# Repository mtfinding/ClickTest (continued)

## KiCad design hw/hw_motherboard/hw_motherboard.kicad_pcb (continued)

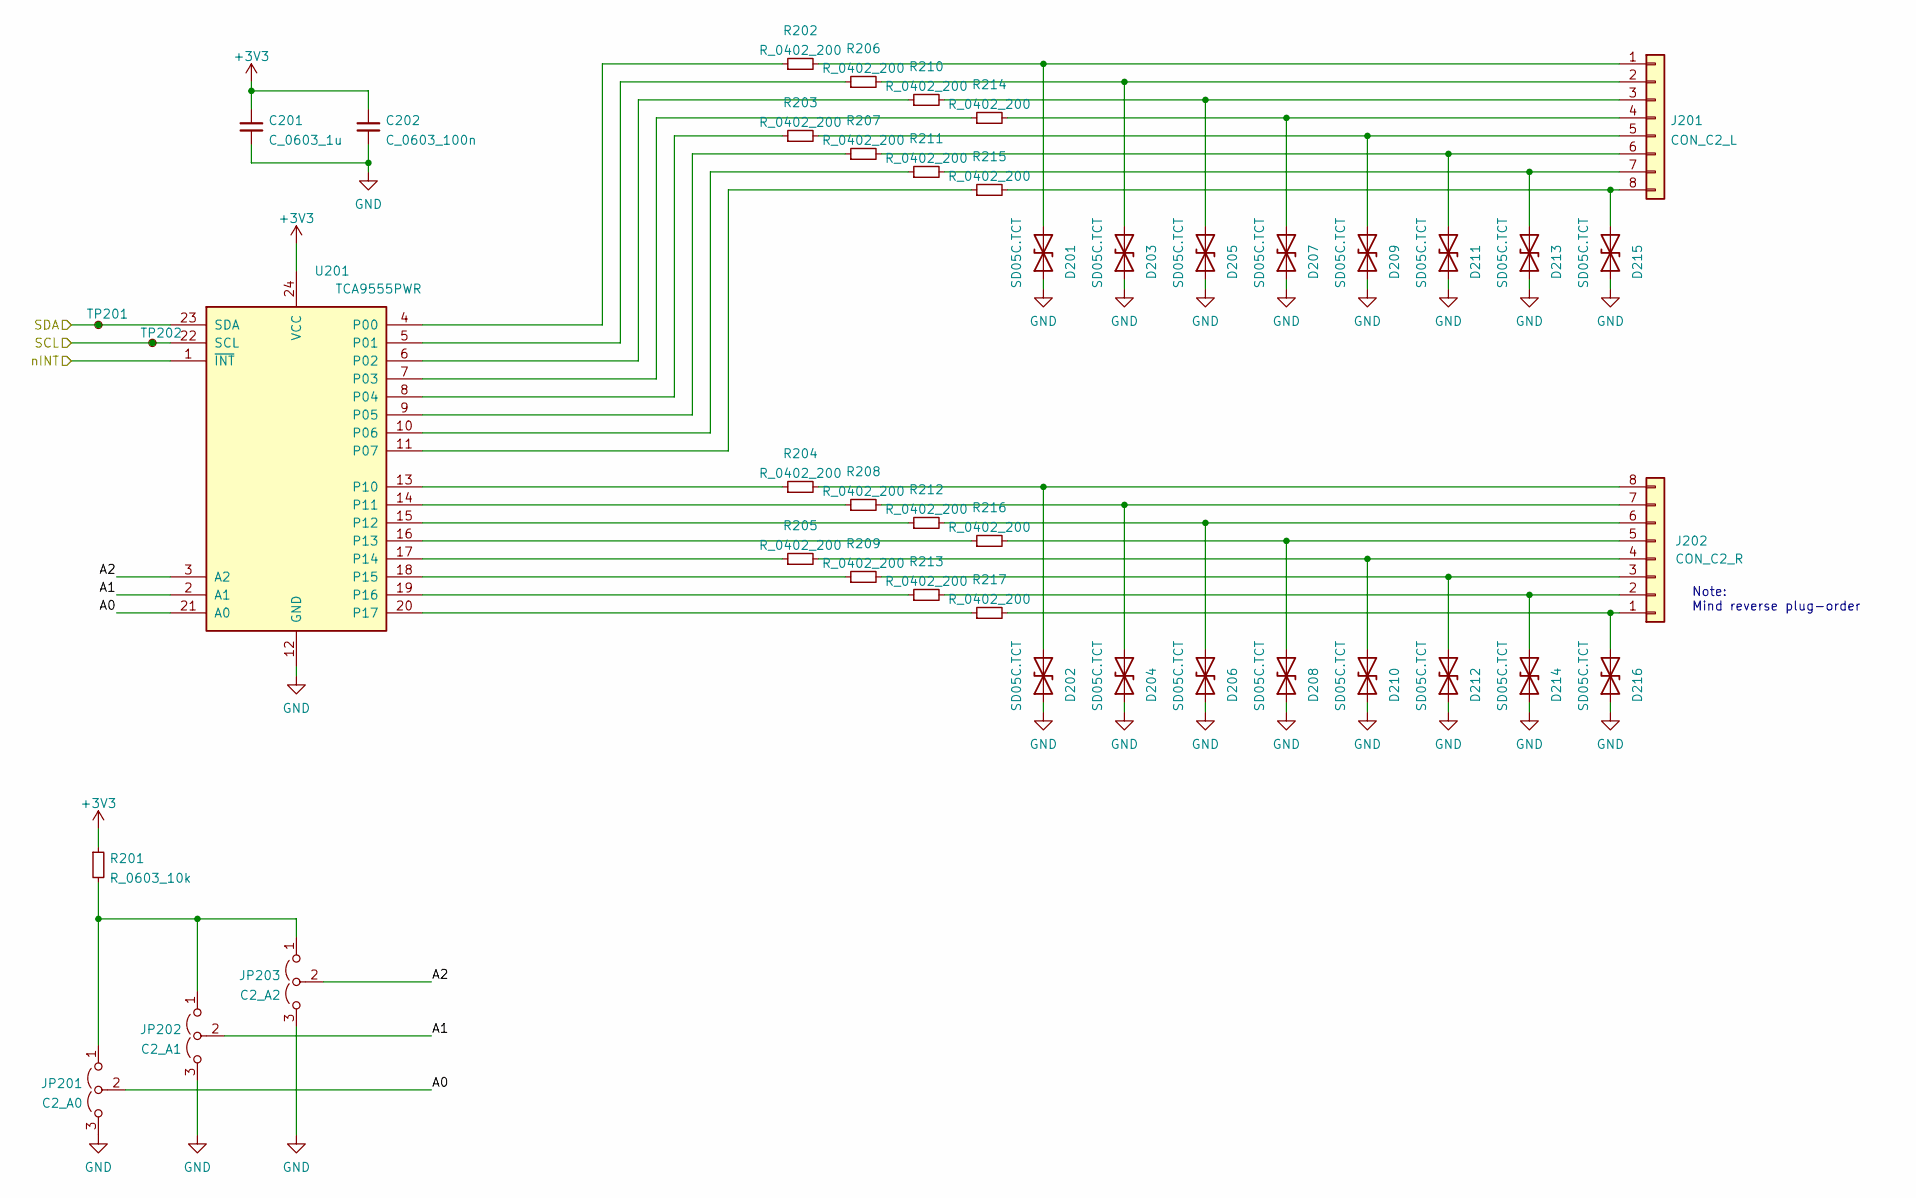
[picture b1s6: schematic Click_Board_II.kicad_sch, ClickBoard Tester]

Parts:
C201: C_0603_1u; C_0603_1608Metric; LCSC Part # C15849
C202: C_0603_100n; C_0603_1608Metric; LCSC Part # C14663
D201, D202, D203, D204, D205, D206, D207, D208, D209, D210, D211, D212, D213, D214, D215, D216: SD05C.TCT; D_SOD-323_HandSoldering; LCSC Part # C85200
J201: CON_C2_L; PinHeader_1x08_P2.54mm_Vertical
J202: CON_C2_R; PinHeader_1x08_P2.54mm_Vertical
JP201: C2_A0; SolderJumper-3_P1.3mm_Open_RoundedPad1.0x1.5mm
JP202: C2_A1; SolderJumper-3_P1.3mm_Open_RoundedPad1.0x1.5mm
JP203: C2_A2; SolderJumper-3_P1.3mm_Open_RoundedPad1.0x1.5mm
R201: R_0603_10k; R_0603_1608Metric; LCSC Part # C25804
R202, R203, R204, R205, R206, R207, R208, R209, R210, R211, R212, R213, R214, R215, R216, R217: R_0402_200; R_0402_1005Metric; LCSC Part # C25087
TP201, TP202: TestPoint_Small; TestPoint_Pad_D1.0mm
U201: TCA9555PWR; TSSOP-24_4.4x7.8mm_P0.65mm

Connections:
+3V3: C201.1, C202.1, R201.1, U201.24 (VCC); also elsewhere on the board
/Click_Board_II/A0: JP201.2 (C), U201.21 (A0)
/Click_Board_II/A1: JP202.2 (C), U201.2 (A1)
/Click_Board_II/A2: JP203.2 (C), U201.3 (A2)
/Click_Board_II/SCL: TP202.1, U201.22 (SCL); also elsewhere on the board
/Click_Board_II/SDA: TP201.1, U201.23 (SDA); also elsewhere on the board
/Click_Board_II/nINT: U201.1 (~INT); also elsewhere on the board
GND: C201.2, C202.2, D201.1 (A1), D202.1 (A1), D203.1 (A1), D204.1 (A1), D205.1 (A1), D206.1 (A1), D207.1 (A1), D208.1 (A1), D209.1 (A1), D210.1 (A1), D211.1 (A1), D212.1 (A1), D213.1 (A1), D214.1 (A1), D215.1 (A1), D216.1 (A1), JP201.3 (B), JP202.3 (B), JP203.3 (B), U201.12 (GND); also elsewhere on the board
unnamed: D201.2 (A2), J201.1, R202.2
unnamed: D202.2 (A2), J202.8, R204.2
unnamed: D203.2 (A2), J201.2, R206.2
unnamed: D204.2 (A2), J202.7, R208.2
unnamed: D205.2 (A2), J201.3, R210.2
unnamed: D206.2 (A2), J202.6, R212.2
unnamed: D207.2 (A2), J201.4, R214.2
unnamed: D208.2 (A2), J202.5, R216.2
unnamed: D209.2 (A2), J201.5, R203.2
unnamed: D210.2 (A2), J202.4, R205.2
unnamed: D211.2 (A2), J201.6, R207.2
unnamed: D212.2 (A2), J202.3, R209.2
unnamed: D213.2 (A2), J201.7, R211.2
unnamed: D214.2 (A2), J202.2, R213.2
unnamed: D215.2 (A2), J201.8, R215.2
unnamed: D216.2 (A2), J202.1, R217.2
unnamed: JP201.1 (A), JP202.1 (A), JP203.1 (A), R201.2
unnamed: R202.1, U201.4 (P00)
unnamed: R203.1, U201.8 (P04)
unnamed: R204.1, U201.13 (P10)
unnamed: R205.1, U201.17 (P14)
unnamed: R206.1, U201.5 (P01)
unnamed: R207.1, U201.9 (P05)
unnamed: R208.1, U201.14 (P11)
unnamed: R209.1, U201.18 (P15)
unnamed: R210.1, U201.6 (P02)
unnamed: R211.1, U201.10 (P06)
unnamed: R212.1, U201.15 (P12)
unnamed: R213.1, U201.19 (P16)
unnamed: R214.1, U201.7 (P03)
unnamed: R215.1, U201.11 (P07)
unnamed: R216.1, U201.16 (P13)
unnamed: R217.1, U201.20 (P17)

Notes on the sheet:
Note: Mind reverse plug-order

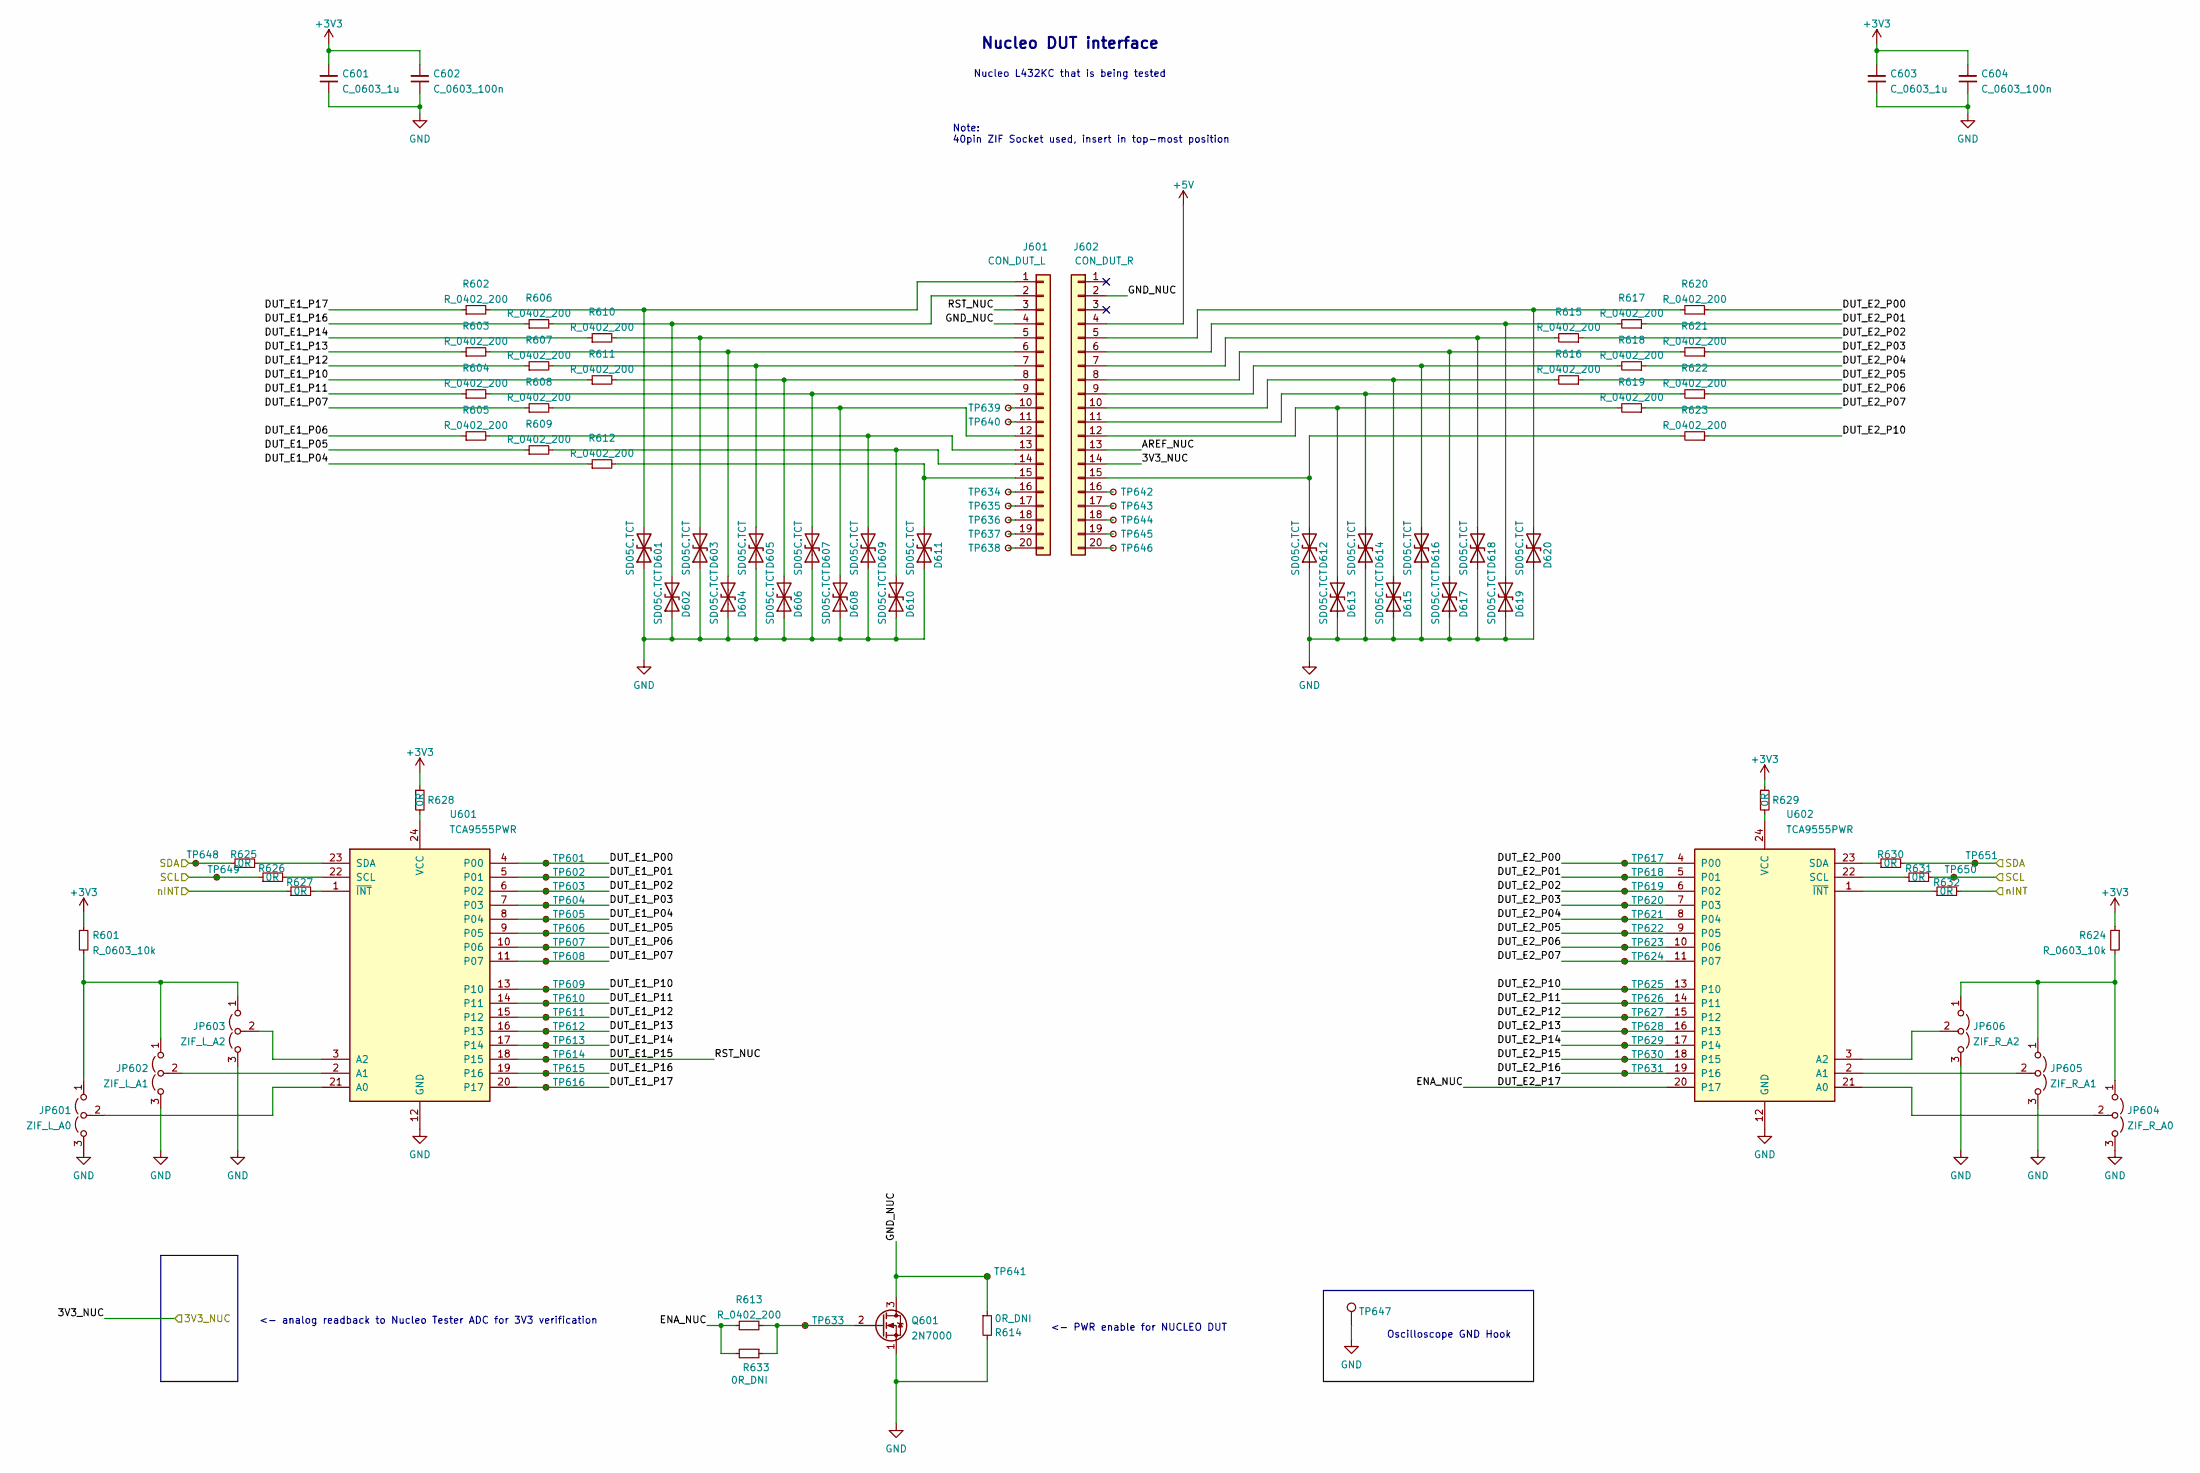
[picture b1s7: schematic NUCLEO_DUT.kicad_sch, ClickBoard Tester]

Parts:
C601, C603: C_0603_1u; C_0603_1608Metric; LCSC Part # C15849
C602, C604: C_0603_100n; C_0603_1608Metric; LCSC Part # C14663
D601, D602, D603, D604, D605, D606, D607, D608, D609, D610, D611, D612, D613, D614, D615, D616, D617, D618, D619, D620: SD05C.TCT; D_SOD-323_HandSoldering; LCSC Part # C85200
J601: CON_DUT_L; PinSocket_1x20_P2.54mm_Vertical
J602: CON_DUT_R; PinSocket_1x20_P2.54mm_Vertical
JP601: ZIF_L_A0; SolderJumper-3_P1.3mm_Open_RoundedPad1.0x1.5mm
JP602: ZIF_L_A1; SolderJumper-3_P1.3mm_Open_RoundedPad1.0x1.5mm
JP603: ZIF_L_A2; SolderJumper-3_P1.3mm_Open_RoundedPad1.0x1.5mm
JP604: ZIF_R_A0; SolderJumper-3_P1.3mm_Open_RoundedPad1.0x1.5mm
JP605: ZIF_R_A1; SolderJumper-3_P1.3mm_Open_RoundedPad1.0x1.5mm
JP606: ZIF_R_A2; SolderJumper-3_P1.3mm_Open_RoundedPad1.0x1.5mm
Q601: 2N7000; TO-92_Inline
R601, R624: R_0603_10k; R_0603_1608Metric; LCSC Part # C25804
R602, R603, R604, R605, R606, R607, R608, R609, R610, R611, R612, R613, R615, R616, R617, R618, R619, R620, R621, R622, R623: R_0402_200; R_0402_1005Metric; LCSC Part # C25087
R614, R633: 0R_DNI; R_0603_1608Metric_Pad0.98x0.95mm_HandSolder; LCSC Part # C21189
R625, R626, R627, R628, R629, R630, R631, R632: 0R; R_0603_1608Metric_Pad0.98x0.95mm_HandSolder; LCSC Part # C21189
TP601, TP602, TP603, TP604, TP605, TP606, TP607, TP608, TP609, TP610, TP611, TP612, TP613, TP614, TP615, TP616, TP617, TP618, TP619, TP620, TP621, TP622, TP623, TP624, TP625, TP626, TP627, TP628, TP629, TP630, TP631, TP633, TP634, TP635, TP636, TP637, TP638, TP639, TP640, TP641, TP642, TP643, TP644, TP645, TP646, TP648, TP649, TP650, TP651: TestPoint_Small; TestPoint_Pad_D1.0mm
TP647: TestPoint; TestPoint_Keystone_5000-5004_Miniature
U601, U602: TCA9555PWR; TSSOP-24_4.4x7.8mm_P0.65mm

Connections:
+3V3: C601.1, C602.1, C603.1, C604.1, R601.1, R624.1, R628.1, R629.1; also elsewhere on the board
+5V: J602.4; also elsewhere on the board
/MCU/MCU_PA7: R626.1, R631.2, TP649.1, TP650.1; also elsewhere on the board
/MCU/MCU_PB4: R625.1, R630.2, TP648.1, TP651.1; also elsewhere on the board
/MCU/MCU_PB5: R627.1, R632.2; also elsewhere on the board
/NUCLEO DUT/3V3_NUC: J602.14; also elsewhere on the board
/NUCLEO DUT/AREF_NUC: J602.13
/NUCLEO DUT/DUT_E1_P00: TP601.1, U601.4 (P00)
/NUCLEO DUT/DUT_E1_P01: TP602.1, U601.5 (P01)
/NUCLEO DUT/DUT_E1_P02: TP603.1, U601.6 (P02)
/NUCLEO DUT/DUT_E1_P03: TP604.1, U601.7 (P03)
/NUCLEO DUT/DUT_E1_P04: R612.1, TP605.1, U601.8 (P04)
/NUCLEO DUT/DUT_E1_P05: R609.1, TP606.1, U601.9 (P05)
/NUCLEO DUT/DUT_E1_P06: R605.1, TP607.1, U601.10 (P06)
/NUCLEO DUT/DUT_E1_P07: R608.1, TP608.1, U601.11 (P07)
/NUCLEO DUT/DUT_E1_P10: R611.1, TP609.1, U601.13 (P10)
/NUCLEO DUT/DUT_E1_P11: R604.1, TP610.1, U601.14 (P11)
/NUCLEO DUT/DUT_E1_P12: R607.1, TP611.1, U601.15 (P12)
/NUCLEO DUT/DUT_E1_P13: R603.1, TP612.1, U601.16 (P13)
/NUCLEO DUT/DUT_E1_P14: R610.1, TP613.1, U601.17 (P14)
/NUCLEO DUT/DUT_E1_P15: J601.3, TP614.1, U601.18 (P15)
/NUCLEO DUT/DUT_E1_P16: R606.1, TP615.1, U601.19 (P16)
/NUCLEO DUT/DUT_E1_P17: R602.1, TP616.1, U601.20 (P17)
/NUCLEO DUT/DUT_E2_P00: R620.1, TP617.1, U602.4 (P00)
/NUCLEO DUT/DUT_E2_P01: R617.1, TP618.1, U602.5 (P01)
/NUCLEO DUT/DUT_E2_P02: R615.1, TP619.1, U602.6 (P02)
/NUCLEO DUT/DUT_E2_P03: R621.1, TP620.1, U602.7 (P03)
/NUCLEO DUT/DUT_E2_P04: R618.1, TP621.1, U602.8 (P04)
/NUCLEO DUT/DUT_E2_P05: R616.1, TP622.1, U602.9 (P05)
/NUCLEO DUT/DUT_E2_P06: R622.1, TP623.1, U602.10 (P06)
/NUCLEO DUT/DUT_E2_P07: R619.1, TP624.1, U602.11 (P07)
/NUCLEO DUT/DUT_E2_P10: R623.1, TP625.1, U602.13 (P10)
/NUCLEO DUT/DUT_E2_P11: TP626.1, U602.14 (P11)
/NUCLEO DUT/DUT_E2_P12: TP627.1, U602.15 (P12)
/NUCLEO DUT/DUT_E2_P13: TP628.1, U602.16 (P13)
/NUCLEO DUT/DUT_E2_P14: TP629.1, U602.17 (P14)
/NUCLEO DUT/DUT_E2_P15: TP630.1, U602.18 (P15)
/NUCLEO DUT/DUT_E2_P16: TP631.1, U602.19 (P16)
/NUCLEO DUT/DUT_E2_P17: R613.1, R633.2, U602.20 (P17)
/NUCLEO DUT/GND_NUC: J601.4, J602.2, Q601.3 (D), R614.1, TP641.1
GND: C601.2, C602.2, C603.2, C604.2, D601.1 (A1), D602.1 (A1), D603.1 (A1), D604.1 (A1), D605.1 (A1), D606.1 (A1), D607.1 (A1), D608.1 (A1), D609.1 (A1), D610.1 (A1), D611.1 (A1), D612.1 (A1), D613.1 (A1), D614.1 (A1), D615.1 (A1), D616.1 (A1), D617.1 (A1), D618.1 (A1), D619.1 (A1), D620.1 (A1), JP601.3 (B), JP602.3 (B), JP603.3 (B), JP604.3 (B), JP605.3 (B), JP606.3 (B), Q601.1 (S), R614.2, TP647.1, U601.12 (GND), U602.12 (GND); also elsewhere on the board
unnamed: D601.2 (A2), J601.1, R602.2
unnamed: D602.2 (A2), J601.2, R606.2
unnamed: D603.2 (A2), J601.5, R610.2
unnamed: D604.2 (A2), J601.6, R603.2
unnamed: D605.2 (A2), J601.7, R607.2
unnamed: D606.2 (A2), J601.8, R611.2
unnamed: D607.2 (A2), J601.9, R604.2
unnamed: D608.2 (A2), J601.12, R608.2
unnamed: D609.2 (A2), J601.13, R605.2
unnamed: D610.2 (A2), J601.14, R609.2
unnamed: D611.2 (A2), J601.15, R612.2
unnamed: D612.2 (A2), J602.15, R623.2
unnamed: D613.2 (A2), J602.12, R619.2
unnamed: D614.2 (A2), J602.11, R622.2
unnamed: D615.2 (A2), J602.10, R616.2
unnamed: D616.2 (A2), J602.9, R618.2
unnamed: D617.2 (A2), J602.8, R621.2
unnamed: D618.2 (A2), J602.7, R615.2
unnamed: D619.2 (A2), J602.6, R617.2
unnamed: D620.2 (A2), J602.5, R620.2
unnamed: J601.10, TP639.1
unnamed: J601.11, TP640.1
unnamed: J601.16, TP634.1
unnamed: J601.17, TP635.1
unnamed: J601.18, TP636.1
unnamed: J601.19, TP637.1
unnamed: J601.20, TP638.1
unnamed: J602.16, TP642.1
unnamed: J602.17, TP643.1
unnamed: J602.18, TP644.1
unnamed: J602.19, TP645.1
unnamed: J602.20, TP646.1
unnamed: JP601.1 (A), JP602.1 (A), JP603.1 (A), R601.2
unnamed: JP601.2 (C), U601.21 (A0)
unnamed: JP602.2 (C), U601.2 (A1)
unnamed: JP603.2 (C), U601.3 (A2)
unnamed: JP604.1 (A), JP605.1 (A), JP606.1 (A), R624.2
unnamed: JP604.2 (C), U602.21 (A0)
unnamed: JP605.2 (C), U602.2 (A1)
unnamed: JP606.2 (C), U602.3 (A2)
unnamed: Q601.2 (G), R613.2, R633.1, TP633.1
unnamed: R625.2, U601.23 (SDA)
unnamed: R626.2, U601.22 (SCL)
unnamed: R627.2, U601.1 (~INT)
unnamed: R628.2, U601.24 (VCC)
unnamed: R629.2, U602.24 (VCC)
unnamed: R630.1, U602.23 (SDA)
unnamed: R631.1, U602.22 (SCL)
unnamed: R632.1, U602.1 (~INT)

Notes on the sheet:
<- analog readback to Nucleo Tester ADC for 3V3 verification
Nucleo L432KC that is being tested
Oscilloscope GND Hook
<- PWR enable for NUCLEO DUT
Note: 40pin ZIF Socket used, insert in top-most position
Nucleo DUT interface

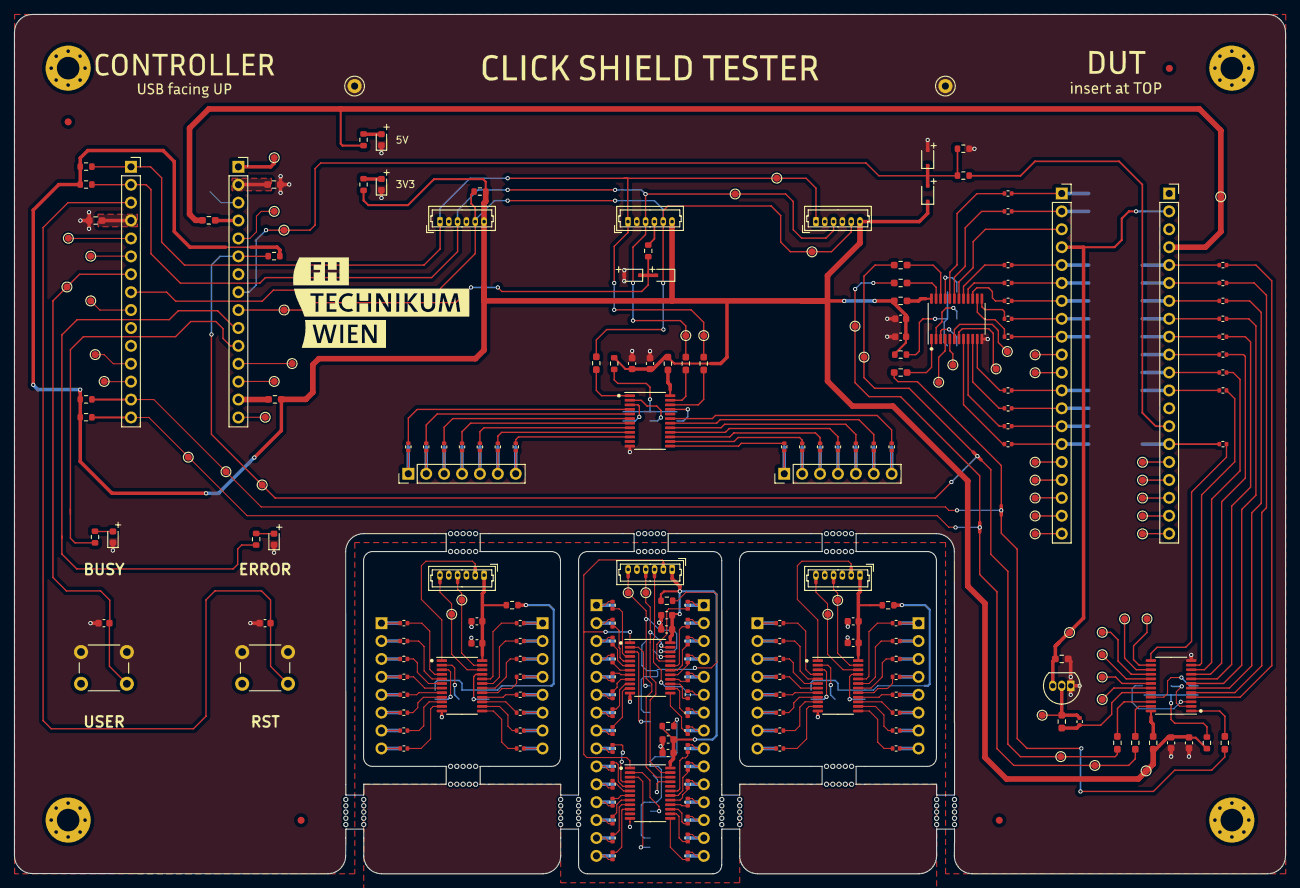
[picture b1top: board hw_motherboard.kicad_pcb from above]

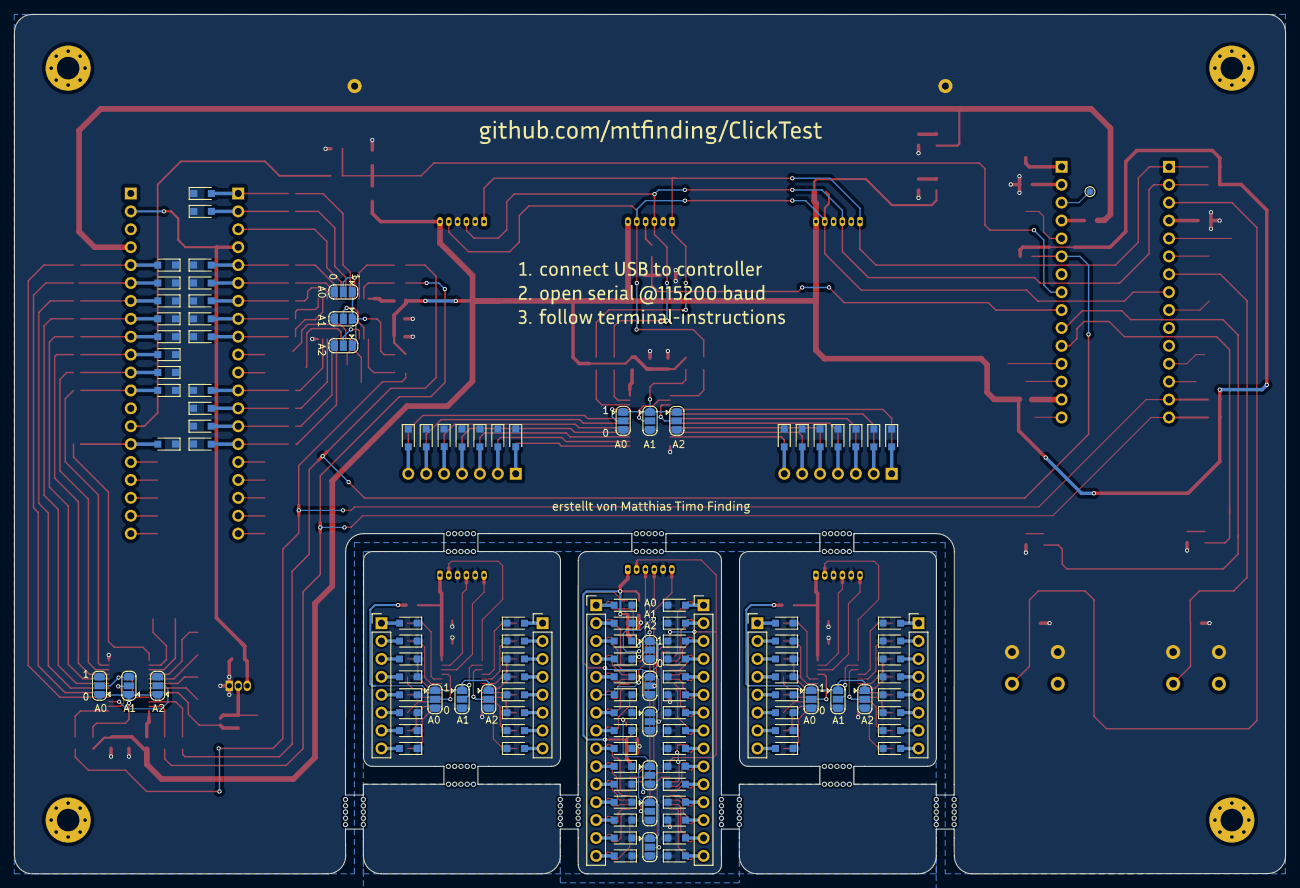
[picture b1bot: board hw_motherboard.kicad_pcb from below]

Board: 2 copper layers, 180.3 x 121.9 mm, 381 parts (124 on the bottom side), 301 nets.
